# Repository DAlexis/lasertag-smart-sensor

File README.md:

# lasertag-smart-sensor
This repository contains hardware and firmware for smart lasertag sensor. Key feature is 3-wire connection (including supply) and absolutely independance of each sensor.

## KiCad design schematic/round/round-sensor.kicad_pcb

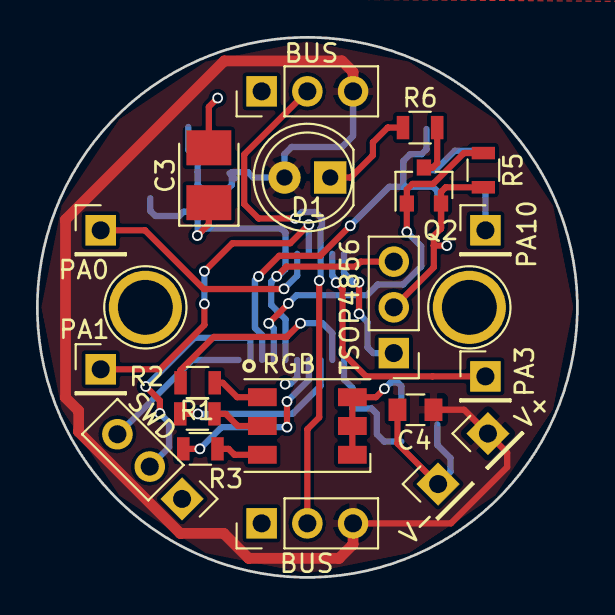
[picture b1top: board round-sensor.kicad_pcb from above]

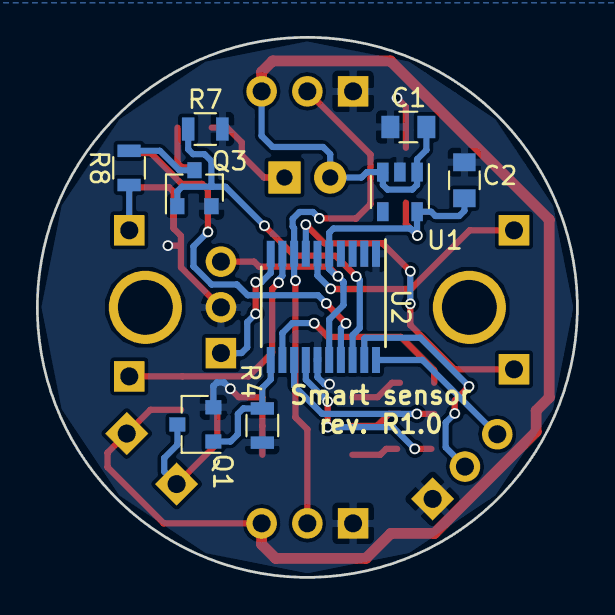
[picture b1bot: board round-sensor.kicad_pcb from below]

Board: 2 copper layers, 30.0 x 30.0 mm, 29 parts (9 on the bottom side), 24 nets.

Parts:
C1, C2, C4: 0.1uF; C_0805
C3: 100uF; CP_Tantalum_Case-B_EIA-3528-21_Reflow
D1: IR; LED_D5.0mm
P1, P2: BUS; Pin_Header_Straight_1x03_Pitch2.54mm
P3: SWD; Pin_Header_Straight_1x03_Pitch2.54mm
P4: PA0; Pin_Header_Straight_1x01_Pitch2.54mm
P5: PA1; Pin_Header_Straight_1x01_Pitch2.54mm
P6: PA3; Pin_Header_Straight_1x01_Pitch2.54mm
P7: PA10; Pin_Header_Straight_1x01_Pitch2.54mm
P8: V+; Pin_Header_Straight_1x01_Pitch2.54mm
P9: V-; Pin_Header_Straight_1x01_Pitch2.54mm
Q1, Q2, Q3: Q_NMOS_GSD; SOT-23
R1, R2, R3: 150; R_0805
R4, R5, R7: 10k; R_0805
R6: R_LED; R_0805
R8: R_load; R_0805
T1: TSOP4856; Pin_Header_Straight_1x03_Pitch2.54mm
U1: NCP551; SOT-23-5
U2: STM32F030F4Px; TSSOP-20_4.4x6.5mm_Pitch0.65mm
U3: RGB; LED_WS2812-PLCC6

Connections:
+3V3: C2.1, C3.1, T1.3, U1.5, U2.5, U2.16
Bus: P1.2, P2.2, U2.8
GND: C1.2, C2.2, C3.2, P1.1, P2.1, P3.1, Q1.2, Q2.2, Q3.2, R4.2, R5.2, R7.2, T1.2, U1.2, U2.1, U2.15, U3.1, U3.2, U3.3
IR_in: T1.1, U2.10
IR_out: Q2.1, R5.1, U2.17
unnamed: C4.2, P9.1, Q1.3
unnamed: D1.1, R6.1
unnamed: P7.1, R8.1
unnamed: Q2.3, R6.2
unnamed: Q3.3, R8.2
unnamed: R1.1, U3.4
unnamed: R2.1, U3.5
unnamed: R3.1, U3.6
PA0: P4.1, U2.6
PA1: P5.1, U2.7
PA3: P6.1, U2.9
PA10: Q3.1, R7.1, U2.18
SDWIO: P3.2, U2.19
SWCLK: P3.3, U2.20
VCC: C1.1, C4.1, D1.2, P1.3, P2.3, P8.1, U1.1, U1.3
Vibro: Q1.1, R4.1, U2.11
blue: R3.2, U2.14
green: R2.2, U2.13
red: R1.2, U2.12

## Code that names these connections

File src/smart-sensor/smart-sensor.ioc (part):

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Mcu.Name=STM32F030F4Px
Mcu.Package=TSSOP20
Mcu.UserName=STM32F030F4Px
PA0.GPIOParameters=GPIO_Label
PA0.GPIO_Label=Tagger_sound
PA0.Signal=GPIO_Output
PA1.Signal=GPIO_Input
PA10.Signal=GPIO_Input
PA13.Mode=Serial_Wire
PA13.Signal=SYS_SWDIO
PA14.Mode=Serial_Wire
PA14.Signal=SYS_SWCLK
PA2.GPIOParameters=GPIO_PuPdOD,GPIO_Label
PA2.GPIO_Label=Bus
PA2.GPIO_PuPdOD=GPIO_NOPULL
PA2.Mode=Half_duplex(single_wire_mode)
PA2.Signal=USART1_TX
PA3.Signal=GPIO_Input
PA4.GPIOParameters=GPIO_PuPd,GPIO_Label
PA4.GPIO_Label=IR_IN
PA4.GPIO_PuPd=GPIO_PULLUP
PA4.Signal=S_TIM14_CH1
PA5.GPIOParameters=GPIO_Label
PA5.GPIO_Label=Vibro
PA5.Signal=GPIO_Output
PA6.GPIOParameters=GPIO_Label
PA6.GPIO_Label=Red
PA6.Signal=S_TIM3_CH1
PA7.GPIOParameters=GPIO_Label
PA7.GPIO_Label=Green
PA7.Signal=S_TIM3_CH2
PA9.GPIOParameters=GPIO_Label
PA9.GPIO_Label=IR_out
PA9.Signal=S_TIM1_CH2
PB1.GPIOParameters=GPIO_Label
PB1.GPIO_Label=Blue
PB1.Signal=S_TIM3_CH4
RCC.SYSCLKFreq_VALUE=16000000
RCC.SYSCLKSource=RCC_SYSCLKSOURCE_PLLCLK
board=smart-sensor

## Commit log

2016-12-25 [firmware] CubeMX project + generated code, CMake. It compiles and flashes
2016-12-25 [firmware] Printf over uart1 works, eclipse project generation
2016-12-25 IR receiver works
2016-12-27 [firmware] SSP implementation beginned
2016-12-28 [emulator] Master PC emulator beginned. Boost asio async serial port used
2016-12-28 [emulator] Emulator code arch improved
2016-12-31 [firmware] Work in progress. SSP interface separated to a different repo
2017-01-01 [emulator] Serial port implementation improved: timeouts are used now
2017-01-02 [emulator] Emulator works with c code
2017-01-02 [emulator] IR requests works
2017-01-02 [emilator] IR buffer receiving works well
2017-01-04 [firmware] Animation controlled from PC works
2017-01-07 [Firmware] Refactoring, only animation works
2017-01-07 [firmware] fixup
2017-01-07 [firmware] IR requests and animation seems stable
2017-01-08 [firmware] Address resolving works
2017-01-27 Some work
2017-02-27 Round sensor PCB done
2017-03-03 PCB improved
2017-03-06 Small square sensor PCB added, minor fix for round
2017-03-10 Round sensor fixed for plexiglass box
2017-03-18 Some improvements. Update in ssp.
2017-03-18 SSP update, little fix
2017-03-18 SSP update
2017-04-08 Fixed ssp library, address based in device id
2017-04-08 Precision clock under construction, Cube source regenerated, animation reset works
2017-05-05 [firmware] [body] Fix for device address generation, fix for RGBs, drawings added
